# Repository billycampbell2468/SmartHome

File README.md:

# SmartHome
All PCB design files and scripts for running my smart home

More info on the project available here:
https://blog.armstrongconsulting.com/a-smart-home-from-scratch/

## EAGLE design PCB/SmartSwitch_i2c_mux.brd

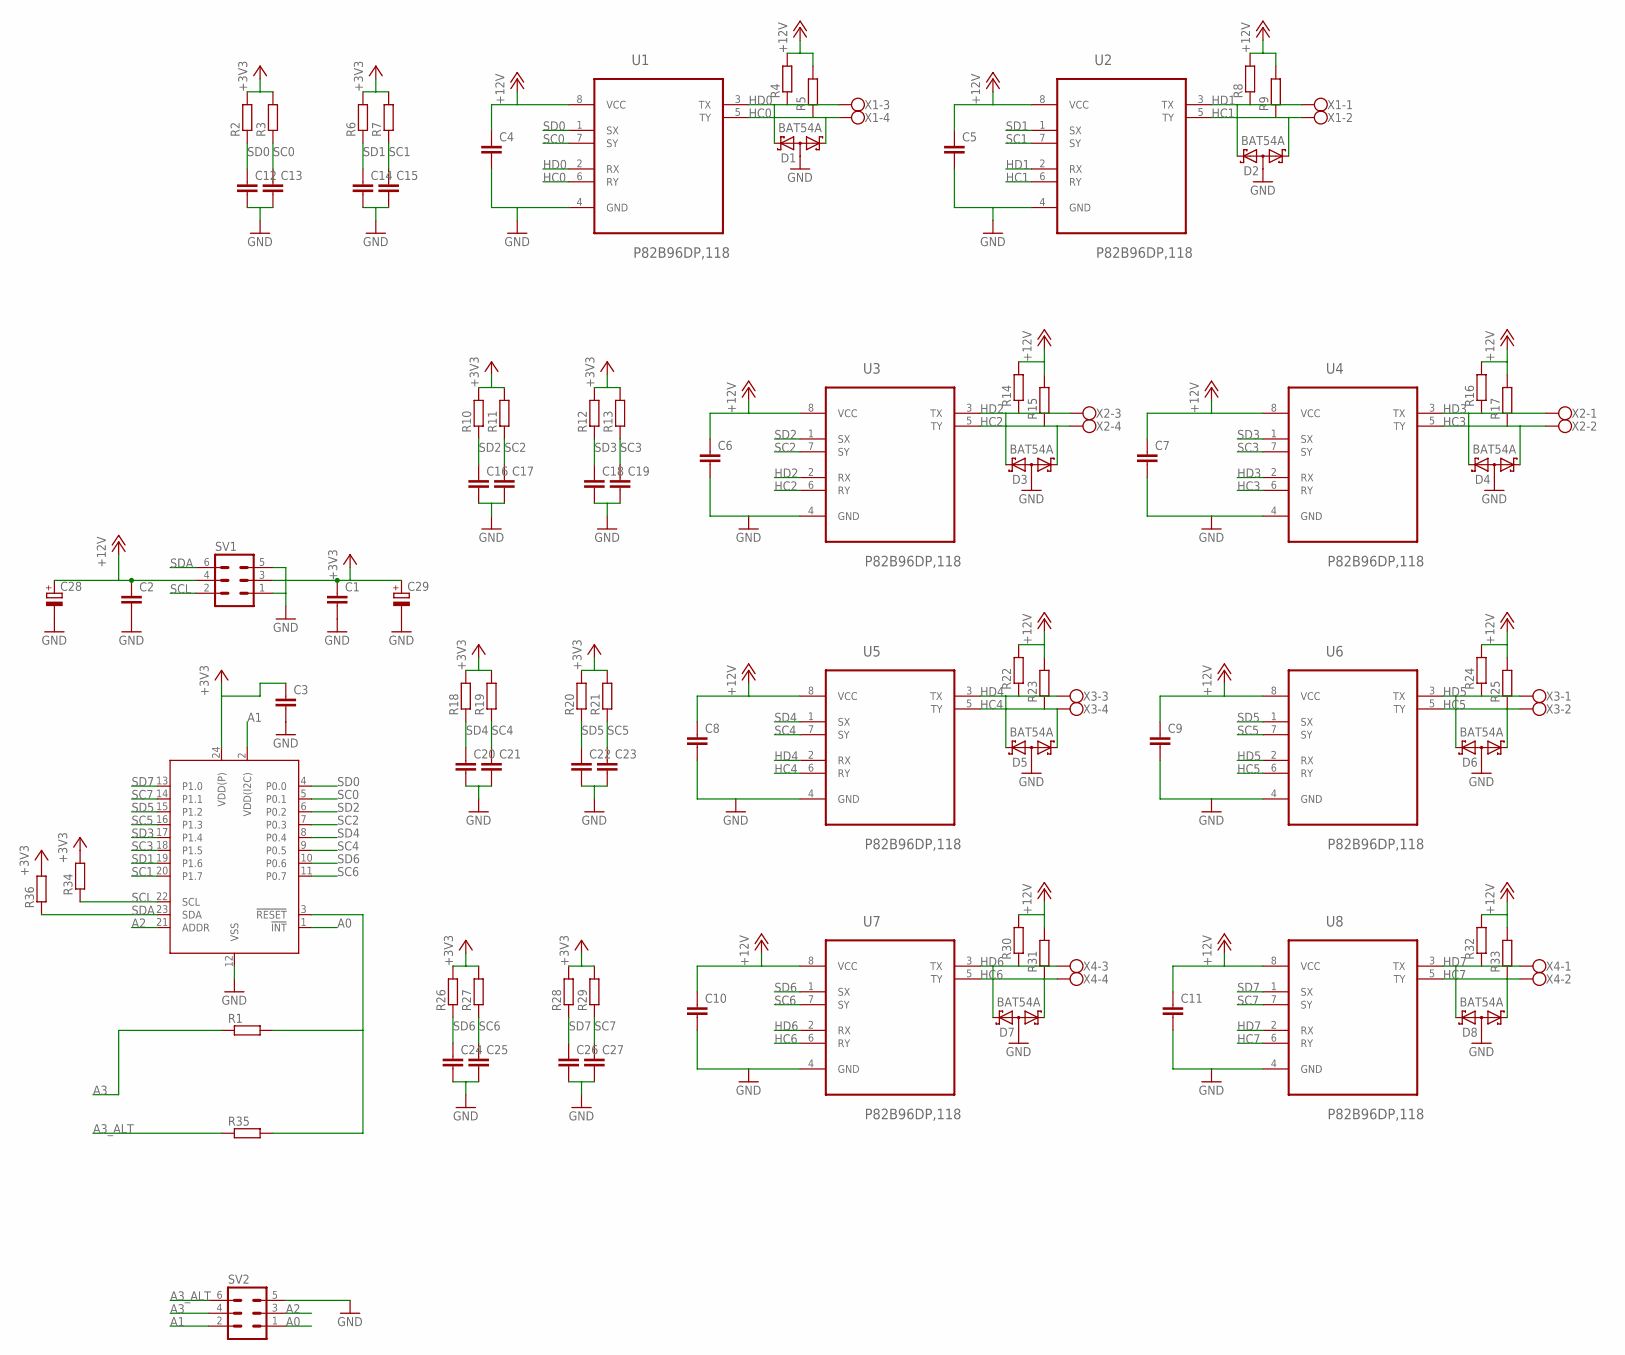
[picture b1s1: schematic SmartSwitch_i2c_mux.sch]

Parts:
C1, C2: C-EUC0805K; C0805K
C3, C4, C5, C6, C7, C8, C9, C10, C11: C-EUC0603K; C0603K
C12, C13, C14, C15, C16, C17, C18, C19, C20, C21, C22, C23, C24, C25, C26, C27: C-EUC0402; C0402
C28, C29: CPOL-EUUD-6,3X7,7; UD-6,3X7,7_NICHICON
D1, D2, D3, D4, D5, D6, D7, D8: BAT54A; SOT23
R1, R35: R-EU_R0402; R0402
R2, R3, R6, R7, R10, R11, R12, R13, R18, R19, R20, R21, R26, R27, R28, R29, R34, R36: R-EU_R0603; R0603
R4, R5, R8, R9, R14, R15, R16, R17, R22, R23, R24, R25, R30, R31, R32, R33: R-EU_R1206; R1206
SV1, SV2: MA03-2
U1, U2, U3, U4, U5, U6, U7, U8: P82B96DP,118; SOP65P490X110-8N
U10: PCAL6416APW; SOT355-1
X1, X2, X3, X4: W237-4

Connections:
+3V3: C1.1, C3.1, C29.+, R2.2, R3.2, R6.2, R7.2, R10.2, R11.2, R12.2, R13.2, R18.2, R19.2, R20.2, R21.2, R26.2, R27.2, R28.2, R29.2, R34.2, R36.2, SV1.3, U10.24 (VDD(P))
+12V: C2.1, C4.1, C5.1, C6.1, C7.1, C8.1, C9.1, C10.1, C11.1, C28.+, R4.2, R5.2, R8.2, R9.2, R14.2, R15.2, R16.2, R17.2, R22.2, R23.2, R24.2, R25.2, R30.2, R31.2, R32.2, R33.2, SV1.4, U1.8 (VCC), U2.8 (VCC), U3.8 (VCC), U4.8 (VCC), U5.8 (VCC), U6.8 (VCC), U7.8 (VCC), U8.8 (VCC)
A0: SV2.1, U10.1 (!INT!)
A1: SV2.2, U10.2 (VDD(I2C))
A2: SV2.3, U10.21 (ADDR)
A3: R1.1, SV2.4
A3_ALT: R35.1, SV2.6
GND: C1.2, C2.2, C3.2, C4.2, C5.2, C6.2, C7.2, C8.2, C9.2, C10.2, C11.2, C12.2, C13.2, C14.2, C15.2, C16.2, C17.2, C18.2, C19.2, C20.2, C21.2, C22.2, C23.2, C24.2, C25.2, C26.2, C27.2, C28.-, C29.-, D1.3 (A1A2), D2.3 (A1A2), D3.3 (A1A2), D4.3 (A1A2), D5.3 (A1A2), D6.3 (A1A2), D7.3 (A1A2), D8.3 (A1A2), SV1.1, SV1.5, SV2.5, U1.4 (GND), U2.4 (GND), U3.4 (GND), U4.4 (GND), U5.4 (GND), U6.4 (GND), U7.4 (GND), U8.4 (GND), U10.12 (VSS)
HC0: D1.1 (K1), R5.1, U1.5 (TY), U1.6 (RY), X1.4
HC1: D2.1 (K1), R9.1, U2.5 (TY), U2.6 (RY), X1.2
HC2: D3.1 (K1), R15.1, U3.5 (TY), U3.6 (RY), X2.4
HC3: D4.1 (K1), R17.1, U4.5 (TY), U4.6 (RY), X2.2
HC4: D5.1 (K1), R23.1, U5.5 (TY), U5.6 (RY), X3.4
HC5: D6.1 (K1), R25.1, U6.5 (TY), U6.6 (RY), X3.2
HC6: D7.1 (K1), R31.1, U7.5 (TY), U7.6 (RY), X4.4
HC7: D8.1 (K1), R33.1, U8.5 (TY), U8.6 (RY), X4.2
HD0: D1.2 (K2), R4.1, U1.2 (RX), U1.3 (TX), X1.3
HD1: D2.2 (K2), R8.1, U2.2 (RX), U2.3 (TX), X1.1
HD2: D3.2 (K2), R14.1, U3.2 (RX), U3.3 (TX), X2.3
HD3: D4.2 (K2), R16.1, U4.2 (RX), U4.3 (TX), X2.1
HD4: D5.2 (K2), R22.1, U5.2 (RX), U5.3 (TX), X3.3
HD5: D6.2 (K2), R24.1, U6.2 (RX), U6.3 (TX), X3.1
HD6: D7.2 (K2), R30.1, U7.2 (RX), U7.3 (TX), X4.3
HD7: D8.2 (K2), R32.1, U8.2 (RX), U8.3 (TX), X4.1
unnamed: R1.2, R35.2, U10.3 (!RESET!)
SC0: C13.1, R3.1, U1.7 (SY), U10.5 (P0.1)
SC1: C15.1, R7.1, U2.7 (SY), U10.20 (P1.7)
SC2: C17.1, R11.1, U3.7 (SY), U10.7 (P0.3)
SC3: C19.1, R13.1, U4.7 (SY), U10.18 (P1.5)
SC4: C21.1, R19.1, U5.7 (SY), U10.9 (P0.5)
SC5: C23.1, R21.1, U6.7 (SY), U10.16 (P1.3)
SC6: C25.1, R27.1, U7.7 (SY), U10.11 (P0.7)
SC7: C27.1, R29.1, U8.7 (SY), U10.14 (P1.1)
SCL: R34.1, SV1.2, U10.22 (SCL)
SD0: C12.1, R2.1, U1.1 (SX), U10.4 (P0.0)
SD1: C14.1, R6.1, U2.1 (SX), U10.19 (P1.6)
SD2: C16.1, R10.1, U3.1 (SX), U10.6 (P0.2)
SD3: C18.1, R12.1, U4.1 (SX), U10.17 (P1.4)
SD4: C20.1, R18.1, U5.1 (SX), U10.8 (P0.4)
SD5: C22.1, R20.1, U6.1 (SX), U10.15 (P1.2)
SD6: C24.1, R26.1, U7.1 (SX), U10.10 (P0.6)
SD7: C26.1, R28.1, U8.1 (SX), U10.13 (P1.0)
SDA: R36.1, SV1.6, U10.23 (SDA)

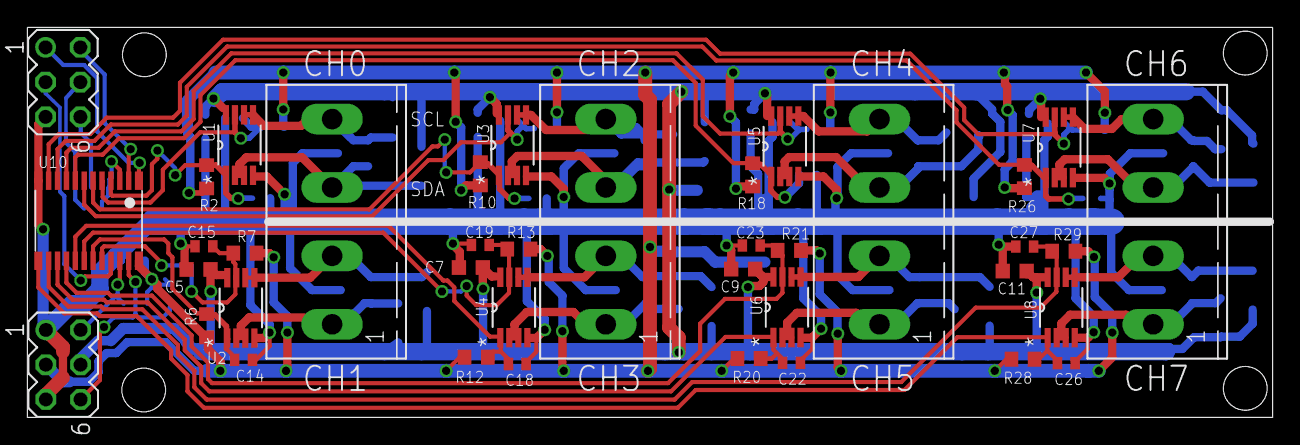
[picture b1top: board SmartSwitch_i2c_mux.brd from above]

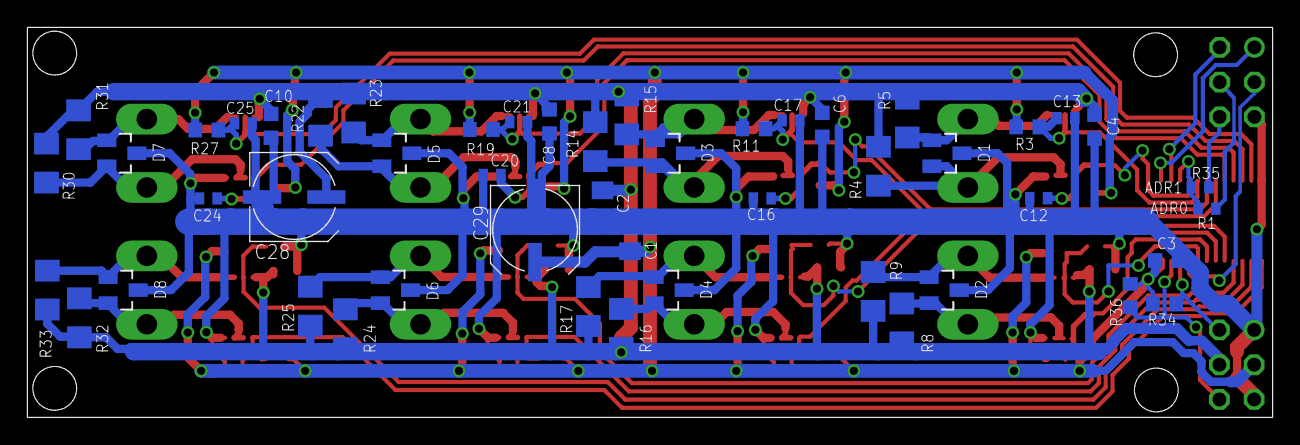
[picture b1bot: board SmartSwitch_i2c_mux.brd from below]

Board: 2 copper layers, 91.0 x 28.5 mm, 88 parts (49 on the bottom side), 43 nets.

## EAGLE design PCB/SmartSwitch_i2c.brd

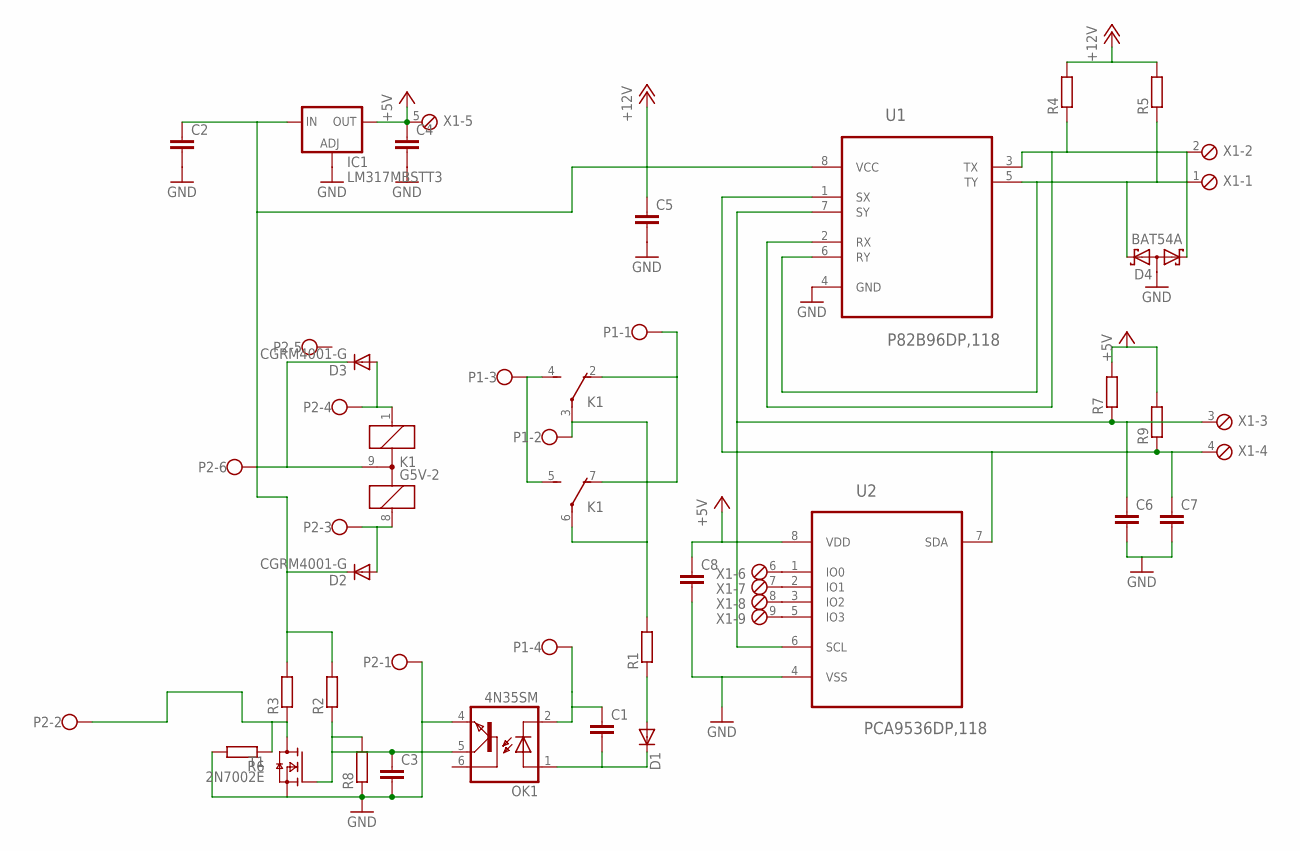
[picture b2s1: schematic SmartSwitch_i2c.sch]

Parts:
C1, C2, C3, C4: C-EUC0805K; C0805K
C5, C8: C-EUC0603K; C0603K
C6, C7: C-EUC0402; C0402
D1: DIODE-DO-214AC; DO-214AC
D2, D3: CGRM4001-G; SOD-123_MINI-SMA
D4: BAT54A; SOT23
IC1: LM317MBSTT3; SOT223
K1: G5V-2
OK1: 4N35SM; DIL6-SMD
P1: W237-4
P2: W237-6
R1, R4, R5: R-EU_R1206; R1206
R2, R3, R6, R7, R8, R9: R-EU_R0603; R0603
T1: 2N7002E; SOT23
U1: P82B96DP,118; SOP65P490X110-8N
U2: PCA9536DP,118; SOP65P490X110-8N
X1: MPT9; 9POL254

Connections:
+5V: C4.1, C8.1, IC1.4 (OUT), R7.2, R9.2, U2.8 (VDD), X1.5
+12V: C2.1, C5.1, D2.C, D3.C, IC1.3 (IN), K1.9 (M), P2.6, R2.2, R3.2, R4.2, R5.2, U1.8 (VCC)
GND: C2.2, C3.2, C4.2, C5.2, C6.2, C7.2, C8.2, D4.3 (A1A2), IC1.1 (ADJ), OK1.4 (EMI), P2.1, R6.2, R8.1, T1.2 (S), U1.4 (GND), U2.4 (VSS)
HCL: D4.2 (K2), R5.1, U1.5 (TY), U1.6 (RY), X1.1
HDA: D4.1 (K1), R4.1, U1.2 (RX), U1.3 (TX), X1.2
unnamed: K1.3, K1.6, P1.2, R1.2
unnamed: K1.4 (S), K1.5 (S), P1.3
unnamed: K1.2 (O), K1.7 (O), P1.1
unnamed: D1.A, R1.1
unnamed: C1.2, D1.C, OK1.1 (A)
unnamed: C1.1, OK1.2 (C), P1.4
unnamed: D3.A, K1.1, P2.4
unnamed: D2.A, K1.8 (2), P2.3
unnamed: C3.1, OK1.5 (COL), R2.1, R8.2, T1.1 (G)
unnamed: P2.2, R3.1, R6.1, T1.3 (D)
unnamed: U2.1 (IO0), X1.6
unnamed: U2.2 (IO1), X1.7
unnamed: U2.3 (IO2), X1.8
unnamed: U2.5 (IO3), X1.9
SCL: C6.1, R7.1, U1.7 (SY), U2.6 (SCL), X1.3
SDA: C7.1, R9.1, U1.1 (SX), U2.7 (SDA), X1.4

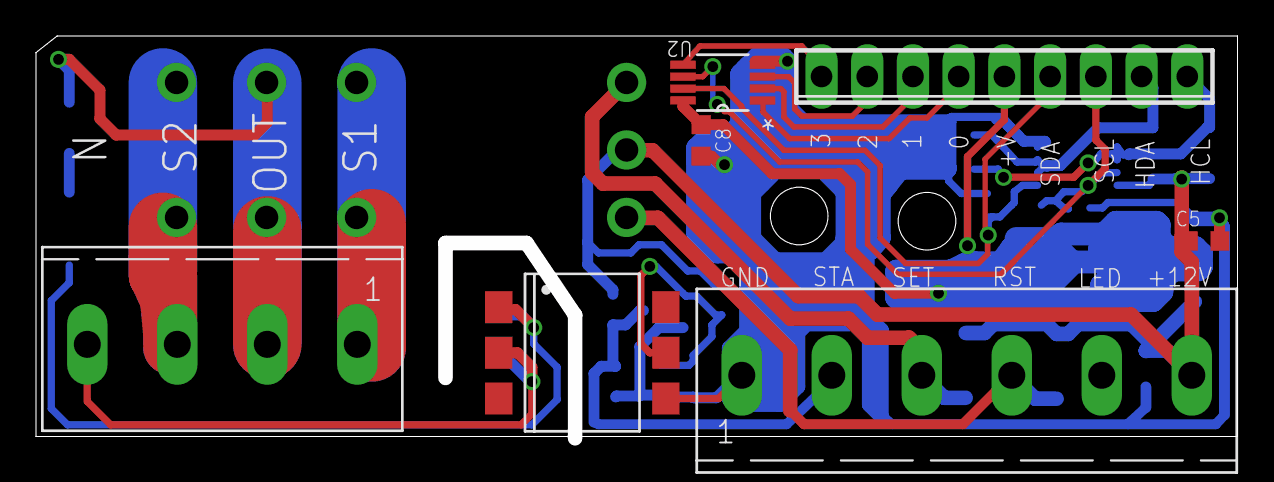
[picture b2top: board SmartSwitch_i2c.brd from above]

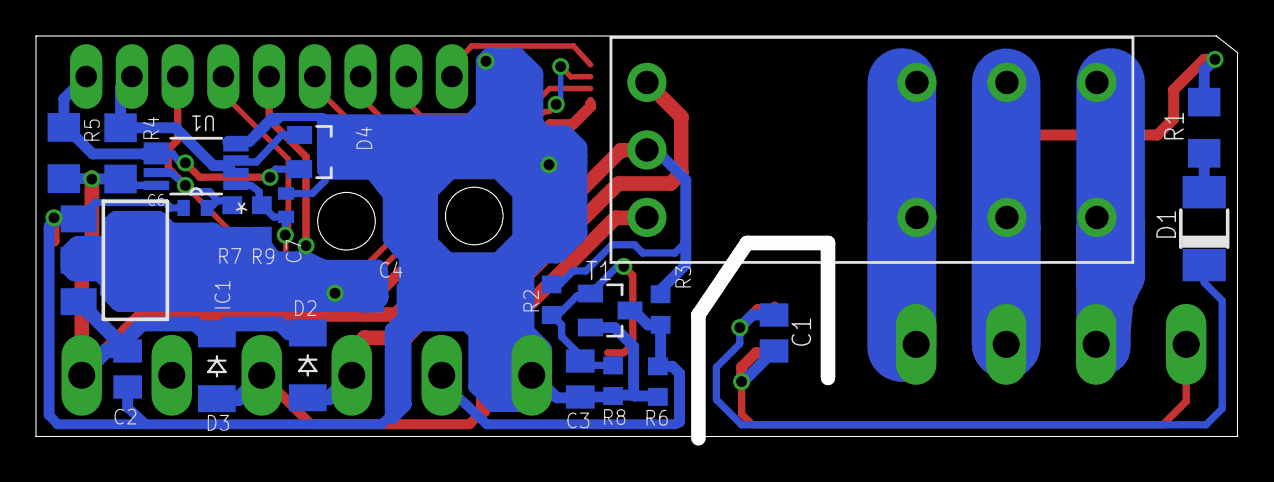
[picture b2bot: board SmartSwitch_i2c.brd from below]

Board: 2 copper layers, 65.9 x 21.9 mm, 30 parts (23 on the bottom side), 21 nets.

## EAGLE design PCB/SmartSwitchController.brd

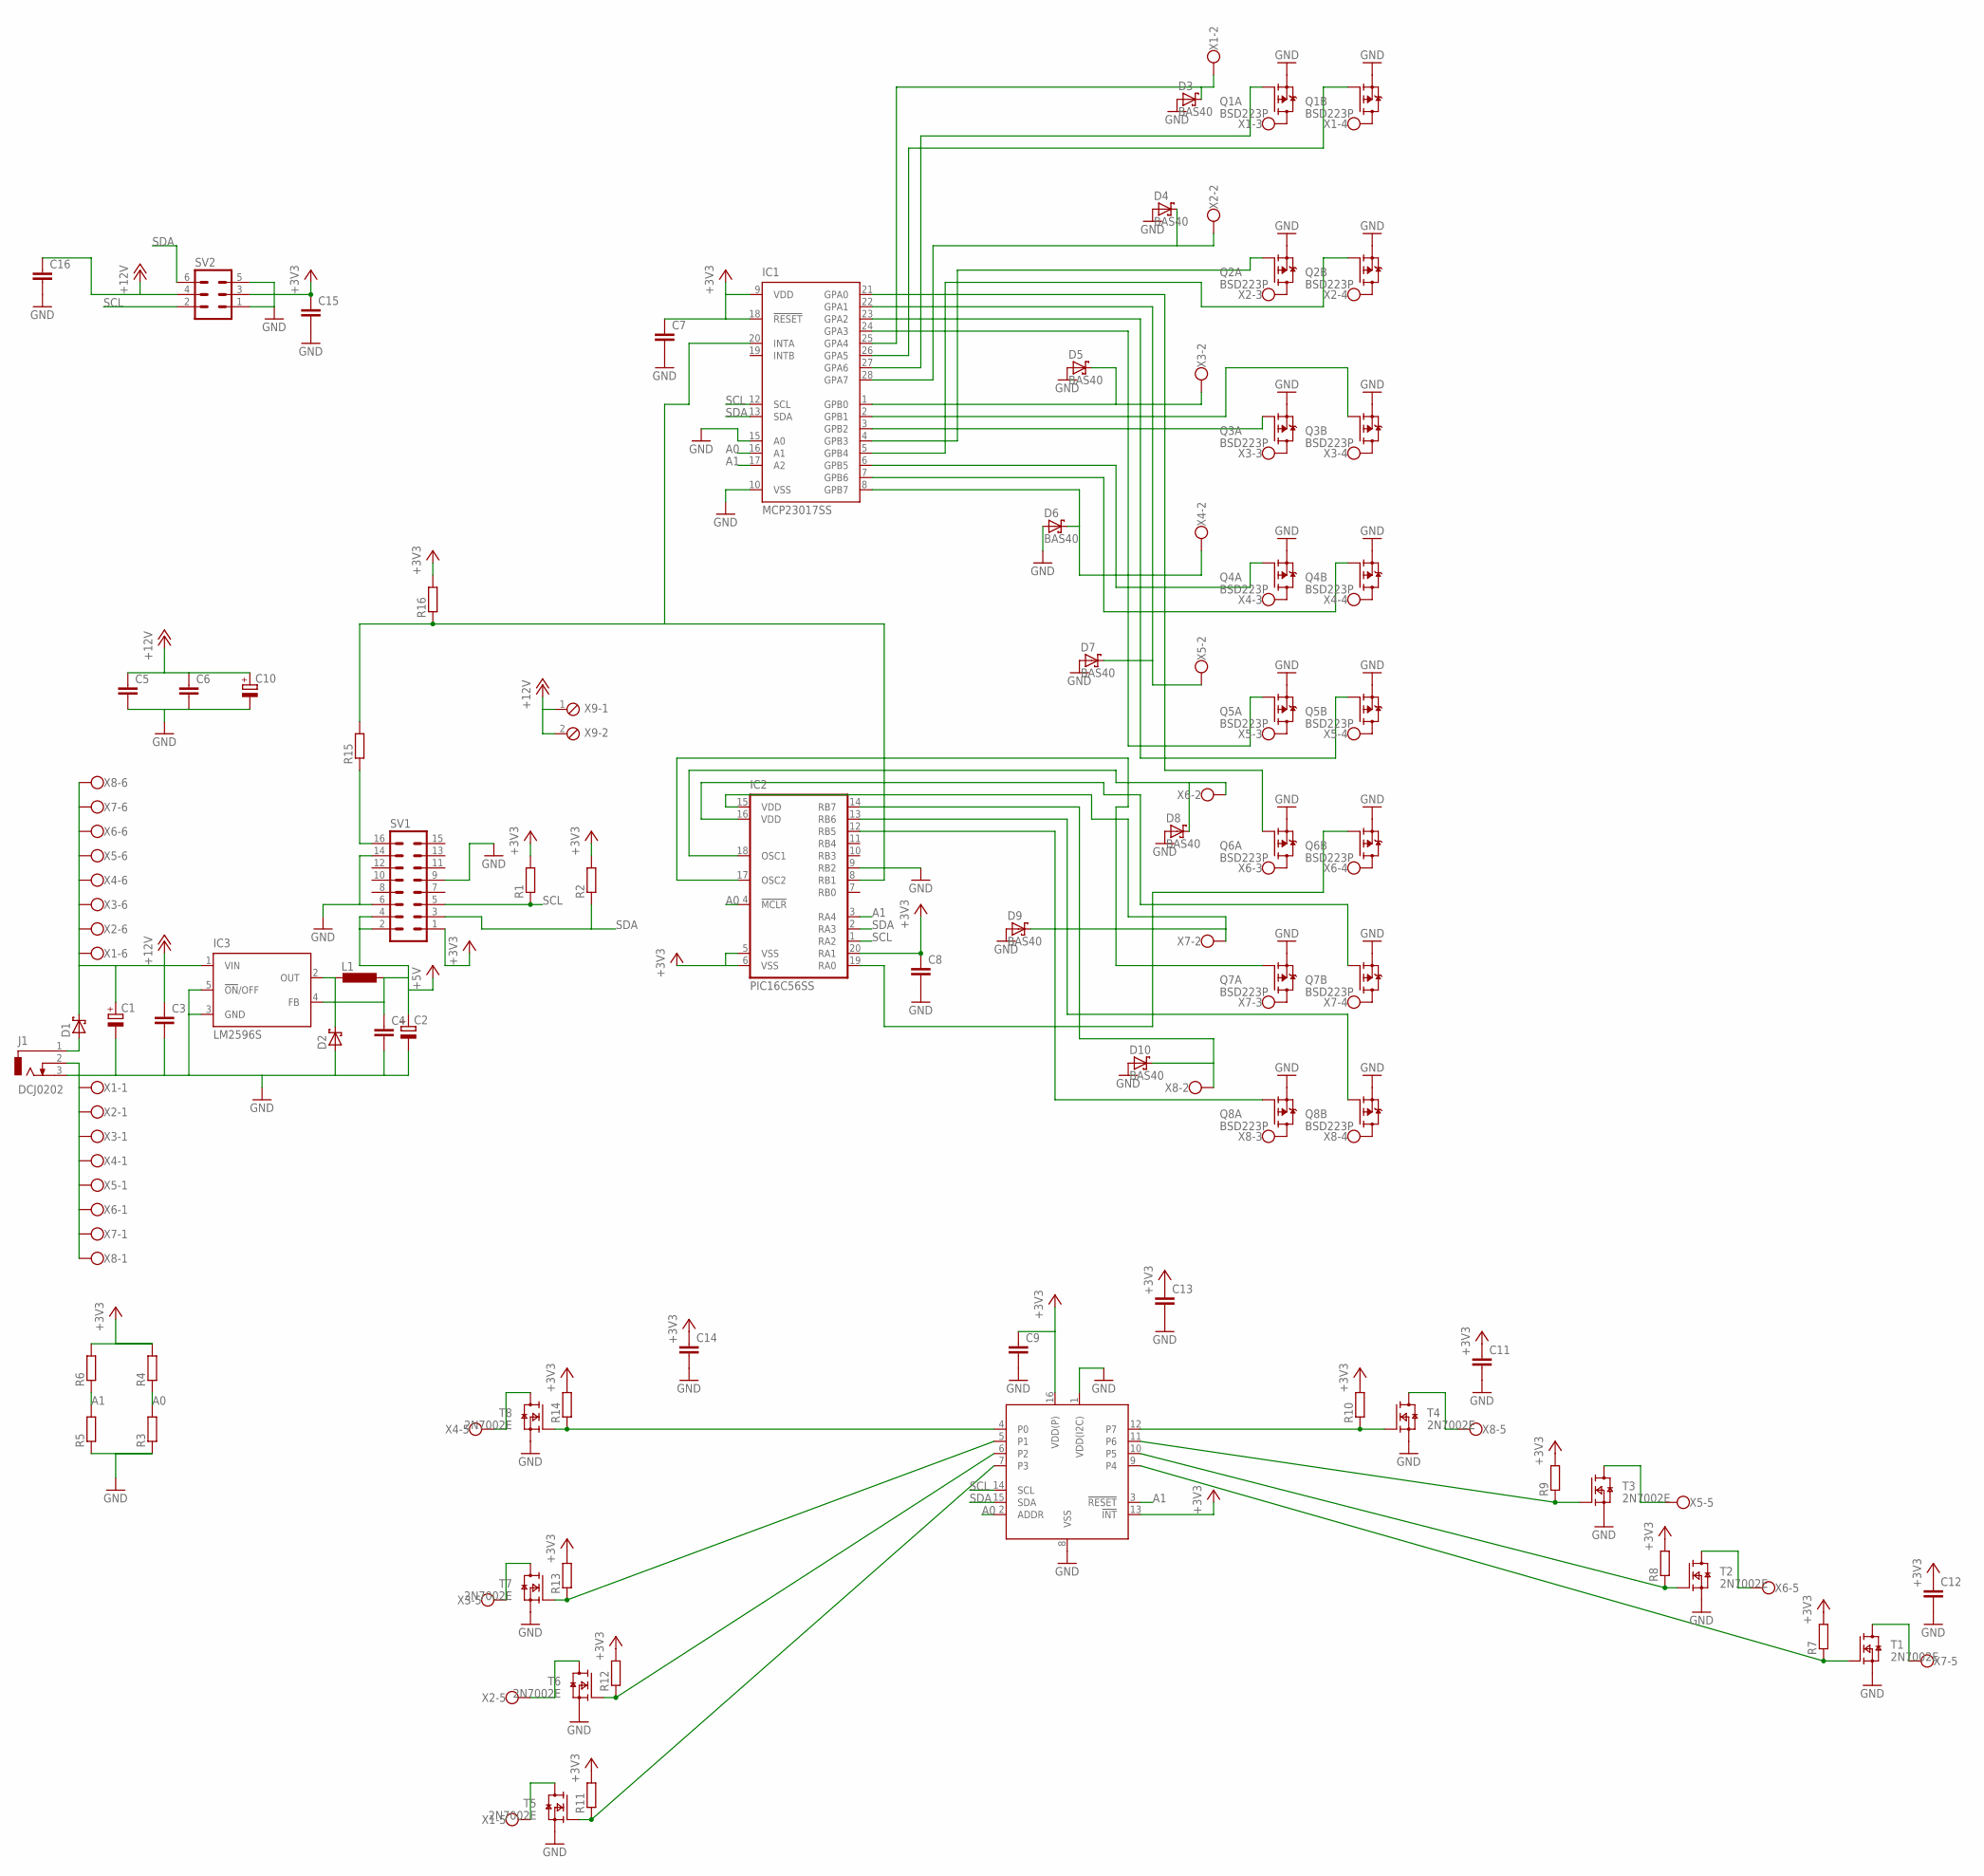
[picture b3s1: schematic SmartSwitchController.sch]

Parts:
C1, C10: CPOL-EUUD-6,3X7,7; UD-6,3X7,7_NICHICON
C2: CPOL-EUUD-10X10; UD-10X10_NICHICON
C3, C4, C5, C7, C8, C9, C11, C12: C-EUC0603; C0603
C6, C13, C14, C15, C16: C-EUC0805; C0805
D1, D2: SCHOTTKY-DIODESMC; SMC
D3, D4, D5, D6, D7, D8, D9, D10: BAS40; SOT23
IC1: MCP23017SS; SSOP28
IC2: PIC16C56SS; SSOP20
IC3: LM2596S; TO263-5
J1: DCJ0202
L1: L-EUL5650M; L5650M
Q1, Q2, Q3, Q4, Q5, Q6, Q7, Q8: BSD223P; SOT363_INFINEON
R1, R2, R15, R16: R-EU_R0603; R0603
R3, R4, R5, R6, R7, R8, R9, R10, R11, R12, R13, R14: R-EU_R0402; R0402
SV1: MA08-2
SV2: MA03-2
T1, T2, T3, T4, T5, T6, T7, T8: 2N7002E; SOT23
U1: PCAL6408APW; SOT403-1
X1, X2, X3, X4, X5, X6, X7, X8: W237-6
X9: MPT2; 2POL254

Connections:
+3V3: C7.1, C8.1, C9.1, C11.1, C12.1, C13.1, C14.1, C15.1, IC1.9 (VDD), IC1.18 (!RESET), IC2.5 (VSS), IC2.6 (VSS), IC2.20 (RA1), R1.2, R2.2, R4.2, R6.2, R7.2, R8.2, R9.2, R10.2, R11.2, R12.2, R13.2, R14.2, R16.2, SV1.1, SV2.3, U1.13 (!INT!), U1.16 (VDD(P))
+5V: C2.+, C4.1, IC3.4 (FB), L1.1, SV1.2, SV1.4
+12V: C1.+, C3.1, C5.1, C6.1, C10.+, C16.1, D1.C, IC3.1 (VIN), SV2.4, X1.6, X2.6, X3.6, X4.6, X5.6, X6.6, X7.6, X8.6, X9.1, X9.2
A0: IC1.16 (A1), IC2.4 (!MCLR), R3.2, R4.1, U1.2 (ADDR)
A1: IC1.17 (A2), IC2.3 (RA4), R5.2, R6.1, U1.3 (!RESET!)
GND: C1.-, C2.-, C3.2, C4.2, C5.2, C6.2, C7.2, C8.2, C9.2, C10.-, C11.2, C12.2, C13.2, C14.2, C15.2, C16.2, D2.A, D3.1 (A), D4.1 (A), D5.1 (A), D6.1 (A), D7.1 (A), D8.1 (A), D9.1 (A), D10.1 (A), IC1.10 (VSS), IC1.15 (A0), IC2.9 (RB2), IC3.3 (GND), IC3.5 (!ON!/OFF), J1.2, J1.3, Q1.1 (S), Q1.4 (S), Q2.1 (S), Q2.4 (S), Q3.1 (S), Q3.4 (S), Q4.1 (S), Q4.4 (S), Q5.1 (S), Q5.4 (S), Q6.1 (S), Q6.4 (S), Q7.1 (S), Q7.4 (S), Q8.1 (S), Q8.4 (S), R3.1, R5.1, SV1.6, SV1.9, SV1.14, SV2.1, SV2.5, T1.2 (S), T2.2 (S), T3.2 (S), T4.2 (S), T5.2 (S), T6.2 (S), T7.2 (S), T8.2 (S), U1.1 (VDD(I2C)), U1.8 (VSS), X1.1, X2.1, X3.1, X4.1, X5.1, X6.1, X7.1, X8.1
unnamed: Q2.3 (D), X2.4
unnamed: Q3.6 (D), X3.3
unnamed: D1.A, J1.1
unnamed: Q1.6 (D), X1.3
unnamed: Q1.3 (D), X1.4
unnamed: Q3.3 (D), X3.4
unnamed: Q2.6 (D), X2.3
unnamed: Q4.6 (D), X4.3
unnamed: D2.C, IC3.2 (OUT), L1.2
unnamed: Q4.3 (D), X4.4
unnamed: Q5.3 (D), X5.4
unnamed: Q5.6 (D), X5.3
unnamed: Q6.6 (D), X6.3
unnamed: Q6.3 (D), X6.4
unnamed: Q7.6 (D), X7.3
unnamed: Q7.3 (D), X7.4
unnamed: Q8.6 (D), X8.3
unnamed: Q8.3 (D), X8.4
unnamed: IC1.21 (GPA0), Q6.2 (G)
unnamed: D7.3 (C), IC1.22 (GPA1), X5.2
unnamed: IC1.23 (GPA2), Q5.5 (G)
unnamed: IC1.24 (GPA3), Q5.2 (G)
unnamed: D3.3 (C), IC1.25 (GPA4), X1.2
unnamed: IC1.26 (GPA5), Q1.5 (G)
unnamed: IC1.27 (GPA6), Q1.2 (G)
unnamed: D4.3 (C), IC1.28 (GPA7), X2.2
unnamed: IC1.5 (GPB4), Q2.5 (G)
unnamed: IC1.4 (GPB3), Q2.2 (G)
unnamed: D5.3 (C), IC1.1 (GPB0), X3.2
unnamed: IC1.2 (GPB1), Q3.5 (G)
unnamed: IC1.3 (GPB2), Q3.2 (G)
unnamed: IC1.6 (GPB5), Q4.2 (G)
unnamed: IC1.7 (GPB6), Q4.5 (G)
unnamed: D6.3 (C), IC1.8 (GPB7), X4.2
unnamed: D9.3 (C), IC2.15 (VDD), X7.2
unnamed: IC2.16 (VDD), Q7.5 (G)
unnamed: IC2.17 (OSC2), Q7.2 (G)
unnamed: D8.3 (C), IC2.18 (OSC1), X6.2
unnamed: IC2.19 (RA0), Q6.5 (G)
unnamed: D10.3 (C), IC2.14 (RB7), X8.2
unnamed: IC2.13 (RB6), Q8.5 (G)
unnamed: IC2.12 (RB5), Q8.2 (G)
unnamed: R11.1, T5.1 (G), U1.7 (P3)
unnamed: R12.1, T6.1 (G), U1.6 (P2)
unnamed: R13.1, T7.1 (G), U1.5 (P1)
unnamed: R14.1, T8.1 (G), U1.4 (P0)
unnamed: R7.1, T1.1 (G), U1.9 (P4)
unnamed: R8.1, T2.1 (G), U1.10 (P5)
unnamed: R9.1, T3.1 (G), U1.11 (P6)
unnamed: R10.1, T4.1 (G), U1.12 (P7)
unnamed: IC1.20 (INTA), IC2.8 (RB1), R15.2, R16.1
unnamed: T1.3 (D), X7.5
unnamed: T2.3 (D), X6.5
unnamed: T3.3 (D), X5.5
unnamed: T4.3 (D), X8.5
unnamed: T5.3 (D), X1.5
unnamed: T6.3 (D), X2.5
unnamed: T7.3 (D), X3.5
unnamed: T8.3 (D), X4.5
unnamed: R15.1, SV1.16
SCL: IC1.12 (SCL), IC2.1 (RA2), R1.1, SV1.5, SV2.2, U1.14 (SCL)
SDA: IC1.13 (SDA), IC2.2 (RA3), R2.1, SV1.3, SV2.6, U1.15 (SDA)

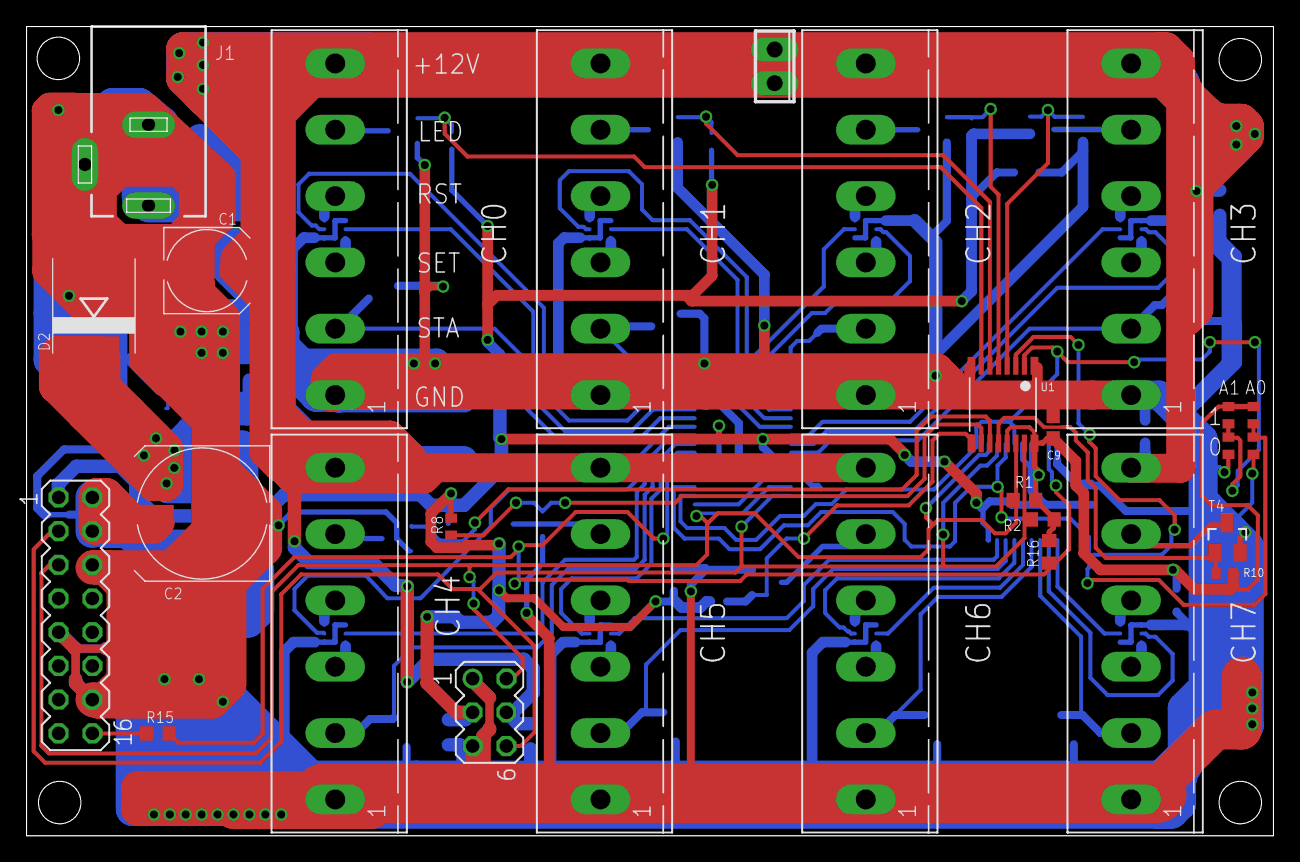
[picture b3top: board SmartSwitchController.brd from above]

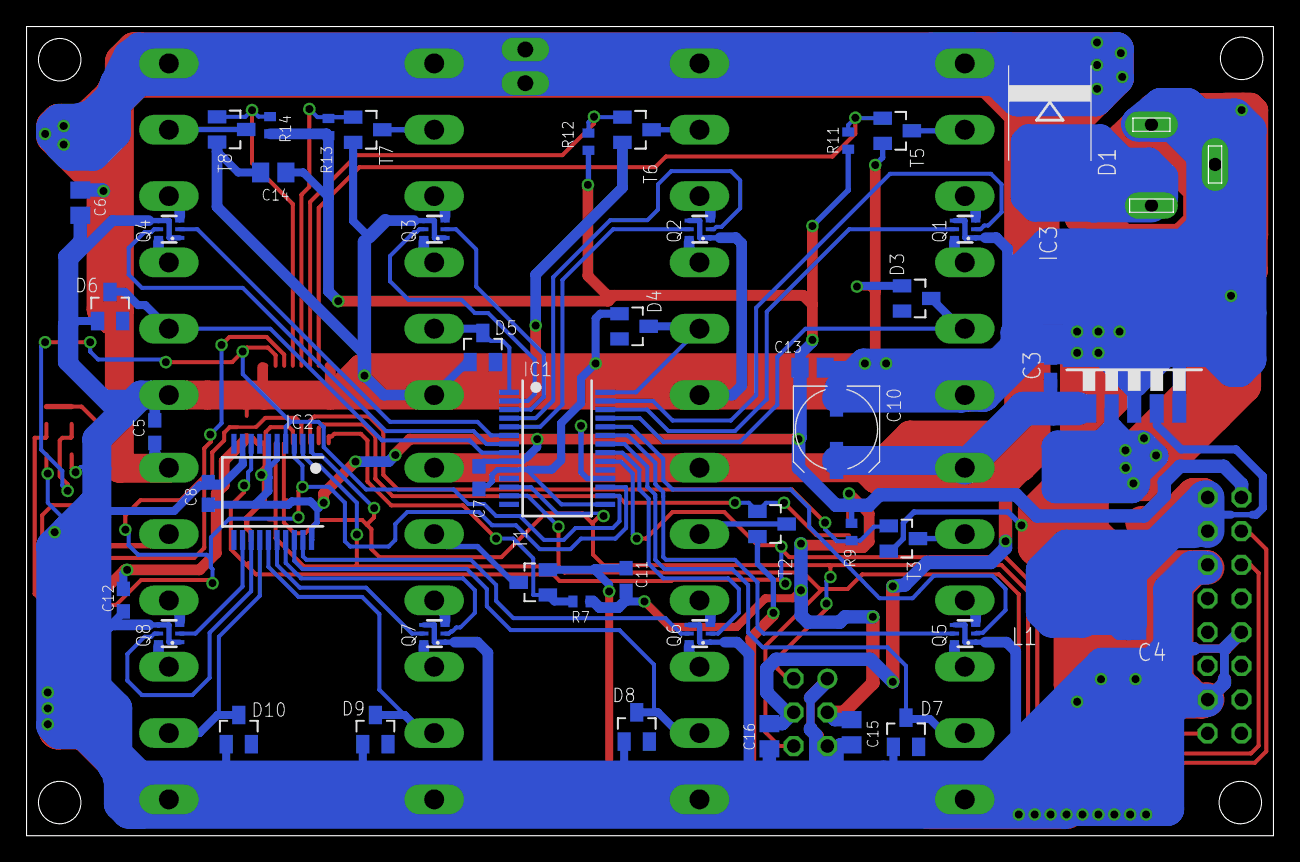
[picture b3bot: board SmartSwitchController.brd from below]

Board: 2 copper layers, 94.0 x 61.0 mm, 75 parts (47 on the bottom side), 68 nets.

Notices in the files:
parts and their libraries:
NXP_60_26022015: This library may be distributed and adapted freely for any purpose, as long as NXP is credited and any new creation is licensed under the same terms.
